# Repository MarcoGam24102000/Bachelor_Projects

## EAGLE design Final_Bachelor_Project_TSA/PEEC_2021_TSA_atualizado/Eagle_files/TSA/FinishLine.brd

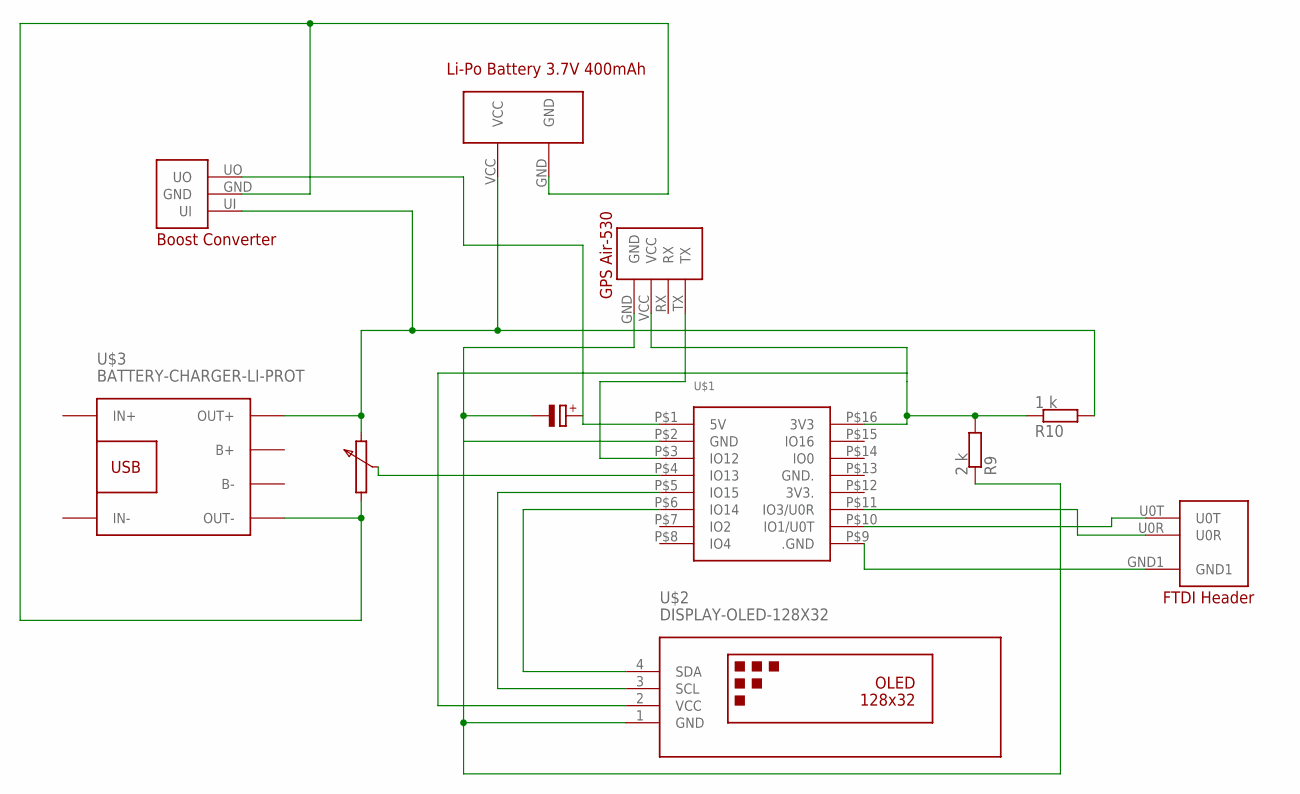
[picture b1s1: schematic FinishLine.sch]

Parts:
R9: 2 k; SMT-REF
R10: 1 k; SMT-REF
U$1: ESP32-CAM
U$2: DISPLAY-OLED-128X32
U$3: BATTERY-CHARGER-LI-PROT
U$4: GPS
U$5: BOOST_CONVERTER
U$6: LIPO_BAT
U$7: HEADER_FTDI

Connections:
unnamed: U$1.P$6 (IO14), U$2.4 (SDA)
unnamed: U$1.P$5 (IO15), U$2.3 (SCL)
unnamed: R9.2, U$1.P$2 (GND), U$2.1 (GND), U$4.GND
unnamed: R9.1, R10.2, U$1.P$16 (3V3), U$2.2 (VCC), U$4.VCC
unnamed: R10.1, U$3.OUT+, U$5.UI, U$6.VCC
unnamed: U$3.OUT-, U$5.GND, U$6.GND
unnamed: U$1.P$1 (5V), U$5.UO
unnamed: U$1.P$9 (.GND), U$7.GND1
unnamed: U$1.P$11 (IO3/U0R), U$7.U0R
unnamed: U$1.P$10 (IO1/U0T), U$7.U0T
unnamed: U$1.P$3 (IO12), U$4.TX

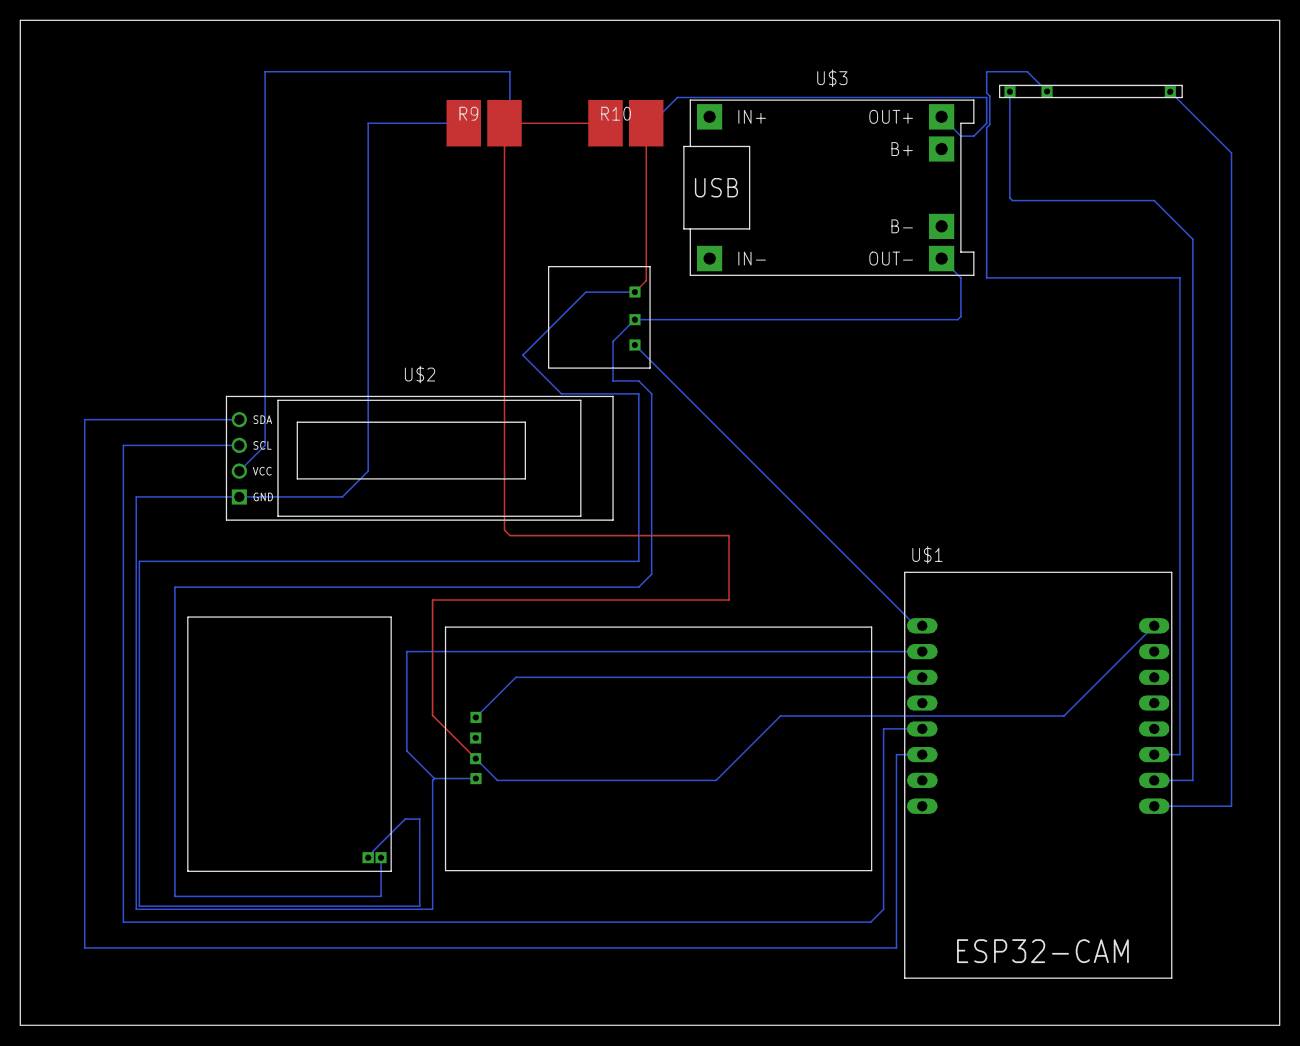
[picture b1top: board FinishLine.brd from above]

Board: 2 copper layers, 124.1 x 99.0 mm, 9 parts (0 on the bottom side), 11 nets.

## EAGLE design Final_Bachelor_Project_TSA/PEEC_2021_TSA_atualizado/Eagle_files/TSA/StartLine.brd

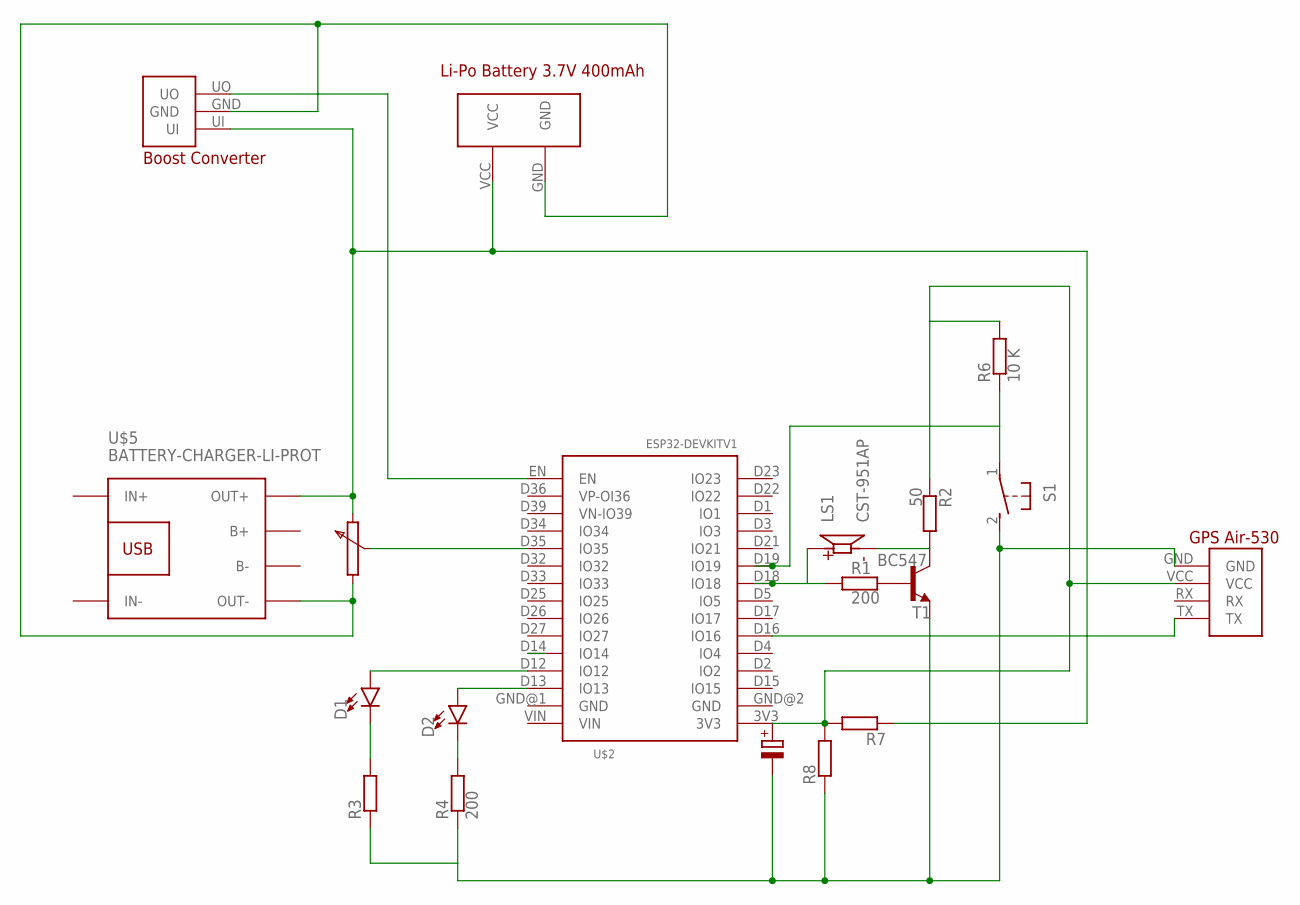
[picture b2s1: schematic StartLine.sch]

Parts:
D1, D2: LED5MM; LED_5MM
LS1: CST-951AP; CUI_CST-951AP
R1, R4: 200; SMT-REF
R2: 50; SMT-REF
R3, R7, R8: SMT-REF
R6: 10 K; SMT-REF
S1: 31-XX; B3F-31XX
T1: BC547; TO92
U$1: BOOST_CONVERTER
U$2: ESP32DEVKITV1; ESP32-DEVKITV1
U$3: GPS
U$4: LIPO_BAT
U$5: BATTERY-CHARGER-LI-PROT

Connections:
unnamed: R1.1, T1.2 (B)
unnamed: R3.2, R4.2, R8.2, S1.2 (S), T1.1 (E), U$3.GND
unnamed: LS1.M, R2.1, T1.3 (C)
unnamed: R1.2, U$2.D18 (IO18)
unnamed: R2.2, R6.1, R7.1, R8.1, U$2.3V3, U$3.VCC
unnamed: R6.2, S1.1
unnamed: U$1.UO, U$2.EN
unnamed: D2.A, U$2.D13 (IO13)
unnamed: D2.K (C), R4.1
unnamed: U$2.D16 (IO16), U$3.TX
unnamed: D1.K (C), R3.1
unnamed: R7.2, U$1.UI, U$4.VCC, U$5.OUT+
unnamed: D1.A, U$2.D12 (IO12)
unnamed: U$1.GND, U$4.GND, U$5.OUT-

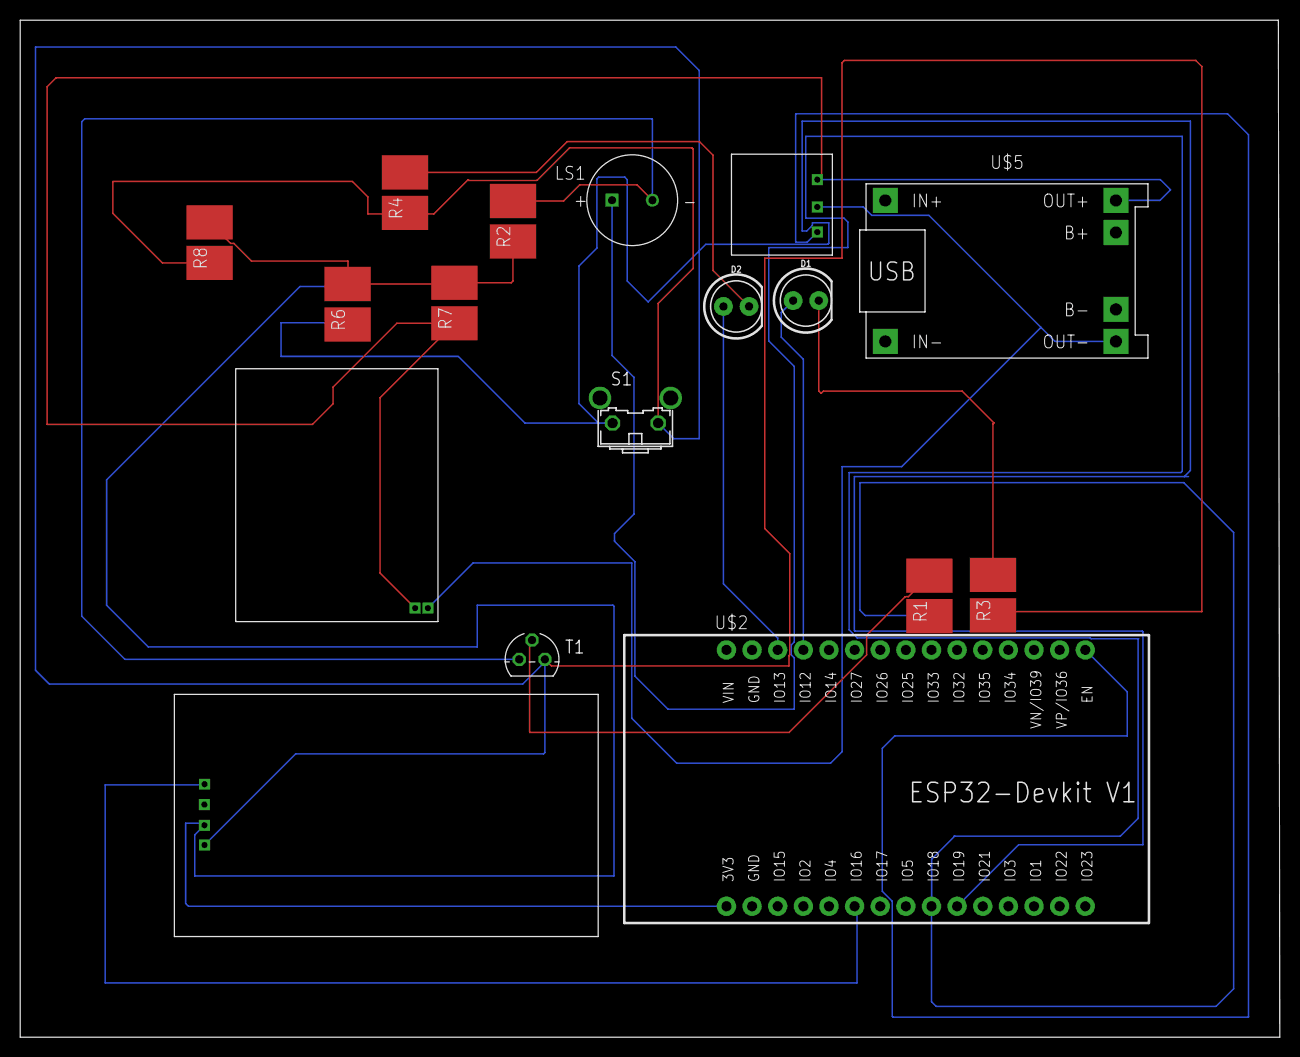
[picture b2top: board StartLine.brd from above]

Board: 2 copper layers, 124.8 x 100.8 mm, 17 parts (0 on the bottom side), 14 nets.

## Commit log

2024-07-07 Add files via upload
    Project developed in the course of Electronic Systems for the Internet of Things, where ESP8266 and ESP32 microcontrollers were used.
2024-07-07 Add files via upload
    Project developed in the Embedded Computational Systems course, utilizing ESP8266 and ESP32 as microprocessors.
2024-07-07 Add files via upload
    Final project for mobile device programming
2024-07-07 Add files via upload
    Final Bachelor Project: TSA - Training Stopwatch for Athletics
2024-07-22 Add files via upload
    Final Project of Mobile Communications

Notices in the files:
parts and their libraries:
diy-modules: Released under the Creative Commons Attribution 4.0 International License: http://creativecommons.org/licenses/by/4.0
SparkFun-LED: Licensing: Creative Commons ShareAlike 4.0 International - https://creativecommons.org/licenses/by-sa/4.0
